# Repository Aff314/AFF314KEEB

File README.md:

# AFF314KEEB
A wireless 36-key low profile non split ergo keyboard.

I started to make this project because I really like using 36-key boards and I've even built two and a handwired board which I designed myself, but never somthing with a PCB. I'm really intersted in those kinds of projects and really like the ones others made but I've never really did one of my own. In the process of designing the board I've learned a lot on how to use KiCad and for the first time I actually documented what I was doing.

I want to thank [Joe Scotto](https://github.com/joe-scotto) for the KiCad footprints and symbols and for the great tutorials on designing a keyboard case and on ZMK.

Additionally I want to thank [GEIST](https://github.com/GEIGEIGEIST) for the Kicad footprints.

And lastly I want to thank [Kumamuk](https://github.com/kumamuk-git) for the CKW12 which made having a roller encoder possible since the EVQWGD001 is way too expensive.

## Instructions on buildung your own
If you want to build your own AFF314KEEB you should start to download the [Gerber file](PCB/Gerber.zip) and upload it to your prefered PCB manufacturing service and order it from there with the PCB from the CKW12 which you can find [here](https://github.com/kumamuk-git/CKW12).

You can find the rest of the parts in the [BOM](BOM.csv).

Once you have sourced all the parts you have to follow the [build guide](BUILDGUIDE.md).

## Partlist

Since I'm from Germany the prices were in EUR and I converted them to USD. Therefore they might not be one hundred percent accurate.

### Parts for the AFF314KEEB

| Item | Qty. | Total Price in USD | Link |
|------|------|--------------------|------|
| NRF52840 NineNano v2 Clone | 1 | 3.77 | https://de.aliexpress.com/item/1005006271779544.html |
| Kailh Choc Hot-Swap Socket | 36 | 6.25 | https://de.aliexpress.com/item/1005008928238101.html |
| Kailh Choc V1 Switch | 36 | 34.24 | https://de.aliexpress.com/item/1005008701630340.html |
| 1N4148W SOD123 | 37 | 1.64 | https://de.aliexpress.com/item/1005006123061230.html |
| IC-Sockets 12pin | 2 | 1.76 | https://de.aliexpress.com/item/1005007476809536.html |
| 3.7 V 301230 | 1 | 4.10 | https://42keebs.eu/shop/parts/lithium-polymer-battery/?attribute_size=301230%20(110%20mAh) |
| SKHLLCA010 | 1 | 0.71 | https://keeb.supply/products/alps-reset-button?variant=e834d428-bed6-4fb3-b94a-90e8f8b87d9b |
| MillMax Pins 3320-0-00-15-00-00-03-0 (optional) | 24 | 3.78 | https://keeb.supply/products/millmax-pins?variant=29bd2804-2a61-4fea-bfe3-f96557a35bd5 |
| PCB | 1 | 14.31 | https://github.com/Aff314/AFF314KEEB/blob/main/PCB/Gerber.zip |
| Any Keycaps for Choc V1 | 36 |  | https://github.com/braindefender/KLP-Lame-Keycaps/tree/master/STEP/Choc%20Stem%20%2B%20Choc%20Size |
| 3D Printed Case | 1 |  | https://github.com/Aff314/AFF314KEEB/tree/main/Case |
| Heatseat insert M2x3x3.5 | 8 | 2.54 | https://de.aliexpress.com/item/1005010362011631.html |
| M2 screws 5mm | 8 | 1.70 | https://de.aliexpress.com/item/1005005070119421.html |

### Parts for the CKW12

| Item | Qty. | Total Price in USD | Link |
|------|------|--------------------|------|
| SMD 3x6x2.5MM Tactile Button | 1 | 1.10 | https://de.aliexpress.com/item/1005008818216326.html |
| EC05E1220202 | 1 | 1.8 | https://de.aliexpress.com/item/1005007146553579.html |
| PCB | 1 | 2.40 | https://github.com/kumamuk-git/CKW12/tree/main/pcb/top |
| 3D Printed Housing | 1 |  | https://github.com/kumamuk-git/CKW12/blob/main/3dmodel/ckw12_housing.stp |
| 3D Printed Stem | 1 |  | https://github.com/kumamuk-git/CKW12/blob/main/3dmodel/ckw12_stem.stl |
| 3D Printed Wheel | 1 |  | https://github.com/kumamuk-git/CKW12/blob/main/3dmodel/ckw12_wheel_fix.stp |

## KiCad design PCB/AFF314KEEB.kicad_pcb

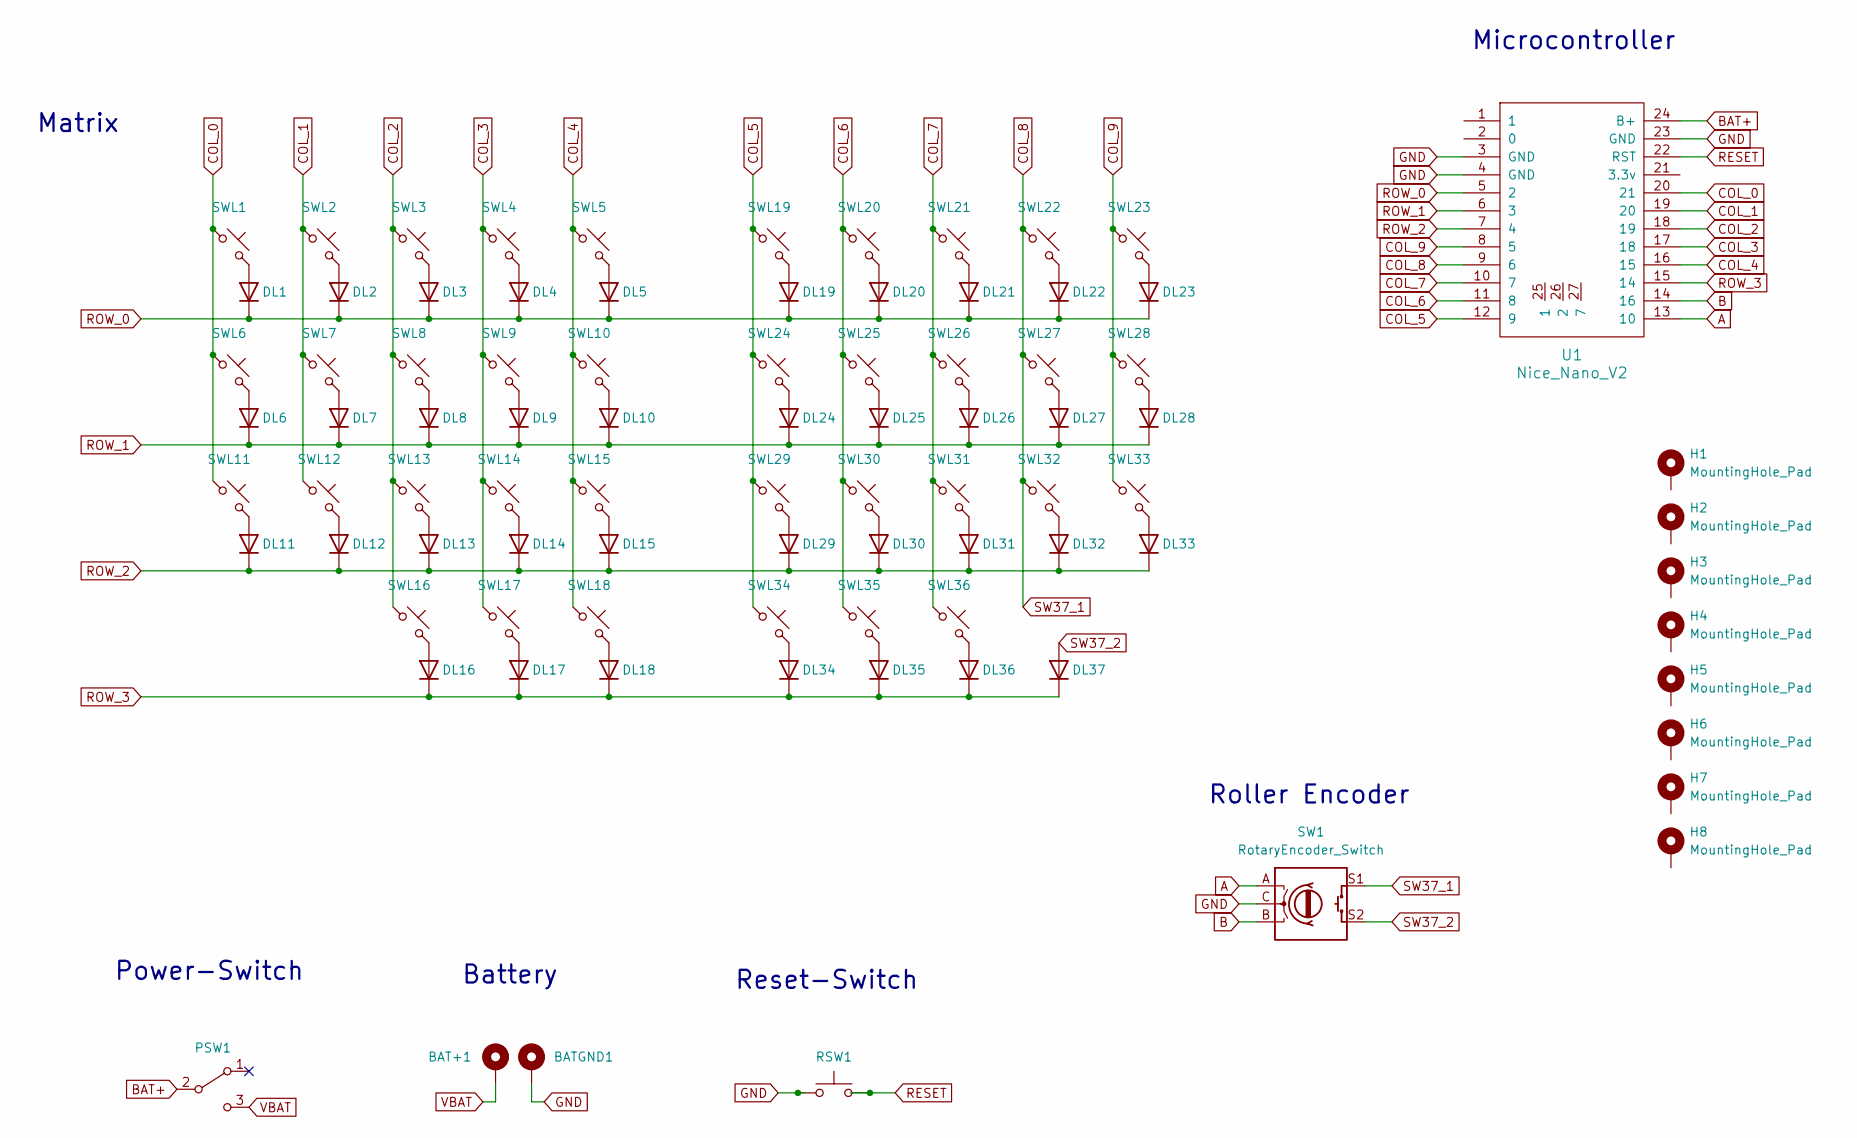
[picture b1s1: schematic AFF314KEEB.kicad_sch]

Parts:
BAT+1: +; BatteryPad
BATGND1: -; BatteryPad
DL1, DL2, DL3, DL4, DL5, DL6, DL7, DL8, DL9, DL10, DL11, DL12, DL13, DL14, DL15, DL16, DL17, DL18, DL19, DL20, DL21, DL22, DL23, DL24, DL25, DL26, DL27, DL28, DL29, DL30, DL31, DL32, DL33, DL34, DL35, DL36, DL37: D; Diode_SOD123
H1, H2, H3, H4, H5, H6, H7, H8: MountingHole_Pad; MountingHole_2.2mm_M2_DIN965_Pad_TopBottom
PSW1: SW_SPDT; MSK12C02
RSW1: SW_Push; SKHLLCA010
SW1: RotaryEncoder_Switch; CKW12
SWL1, SWL2, SWL3, SWL4, SWL5, SWL6, SWL7, SWL8, SWL9, SWL10, SWL11, SWL12, SWL13, SWL14, SWL15, SWL16, SWL17, SWL18, SWL19, SWL20, SWL21, SWL22, SWL23, SWL24, SWL25, SWL26, SWL27, SWL28, SWL29, SWL30, SWL31, SWL32, SWL33, SWL34, SWL35, SWL36: choc_v1_SW_solder; Kailh_socket_PG1350_optional
U1: Nice_Nano_V2; Nice_Nano_V2_Flipped

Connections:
A: SW1.A, U1.13 (10)
B: SW1.B, U1.14 (16)
BAT+: PSW1.2 (B), U1.24 (B+)
COL_0: SWL1.1, SWL6.1, SWL11.1, U1.20 (21)
COL_1: SWL2.1, SWL7.1, SWL12.1, U1.19 (20)
COL_2: SWL3.1, SWL8.1, SWL13.1, SWL16.1, U1.18 (19)
COL_3: SWL4.1, SWL9.1, SWL14.1, SWL17.1, U1.17 (18)
COL_4: SWL5.1, SWL10.1, SWL15.1, SWL18.1, U1.16 (15)
COL_5: SWL19.1, SWL24.1, SWL29.1, SWL34.1, U1.12 (9)
COL_6: SWL20.1, SWL25.1, SWL30.1, SWL35.1, U1.11 (8)
COL_7: SWL21.1, SWL26.1, SWL31.1, SWL36.1, U1.10 (7)
COL_8: SW1.S1, SWL22.1, SWL27.1, SWL32.1, U1.9 (6)
COL_9: SWL23.1, SWL28.1, SWL33.1, U1.8 (5)
GND: BATGND1.1, RSW1.1, SW1.C, U1.3 (GND), U1.4 (GND), U1.23 (GND)
unnamed: DL1.2 (A), SWL1.2
unnamed: DL2.2 (A), SWL2.2
unnamed: DL3.2 (A), SWL3.2
unnamed: DL4.2 (A), SWL4.2
unnamed: DL5.2 (A), SWL5.2
unnamed: DL6.2 (A), SWL6.2
unnamed: DL7.2 (A), SWL7.2
unnamed: DL8.2 (A), SWL8.2
unnamed: DL9.2 (A), SWL9.2
unnamed: DL10.2 (A), SWL10.2
unnamed: DL11.2 (A), SWL11.2
unnamed: DL12.2 (A), SWL12.2
unnamed: DL13.2 (A), SWL13.2
unnamed: DL14.2 (A), SWL14.2
unnamed: DL15.2 (A), SWL15.2
unnamed: DL16.2 (A), SWL16.2
unnamed: DL17.2 (A), SWL17.2
unnamed: DL18.2 (A), SWL18.2
unnamed: DL19.2 (A), SWL19.2
unnamed: DL20.2 (A), SWL20.2
unnamed: DL21.2 (A), SWL21.2
unnamed: DL22.2 (A), SWL22.2
unnamed: DL23.2 (A), SWL23.2
unnamed: DL24.2 (A), SWL24.2
unnamed: DL25.2 (A), SWL25.2
unnamed: DL26.2 (A), SWL26.2
unnamed: DL27.2 (A), SWL27.2
unnamed: DL28.2 (A), SWL28.2
unnamed: DL29.2 (A), SWL29.2
unnamed: DL30.2 (A), SWL30.2
unnamed: DL31.2 (A), SWL31.2
unnamed: DL32.2 (A), SWL32.2
unnamed: DL33.2 (A), SWL33.2
unnamed: DL34.2 (A), SWL34.2
unnamed: DL35.2 (A), SWL35.2
unnamed: DL36.2 (A), SWL36.2
RESET: RSW1.2, U1.22 (RST)
ROW_0: DL1.1 (K), DL2.1 (K), DL3.1 (K), DL4.1 (K), DL5.1 (K), DL19.1 (K), DL20.1 (K), DL21.1 (K), DL22.1 (K), DL23.1 (K), U1.5 (2)
ROW_1: DL6.1 (K), DL7.1 (K), DL8.1 (K), DL9.1 (K), DL10.1 (K), DL24.1 (K), DL25.1 (K), DL26.1 (K), DL27.1 (K), DL28.1 (K), U1.6 (3)
ROW_2: DL11.1 (K), DL12.1 (K), DL13.1 (K), DL14.1 (K), DL15.1 (K), DL29.1 (K), DL30.1 (K), DL31.1 (K), DL32.1 (K), DL33.1 (K), U1.7 (4)
ROW_3: DL16.1 (K), DL17.1 (K), DL18.1 (K), DL34.1 (K), DL35.1 (K), DL36.1 (K), DL37.1 (K), U1.15 (14)
SW37_2: DL37.2 (A), SW1.S2
VBAT: BAT+1.1, PSW1.3 (C)

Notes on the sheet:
Battery
Matrix
Reset-Switch
Microcontroller
Roller Encoder
Power-Switch

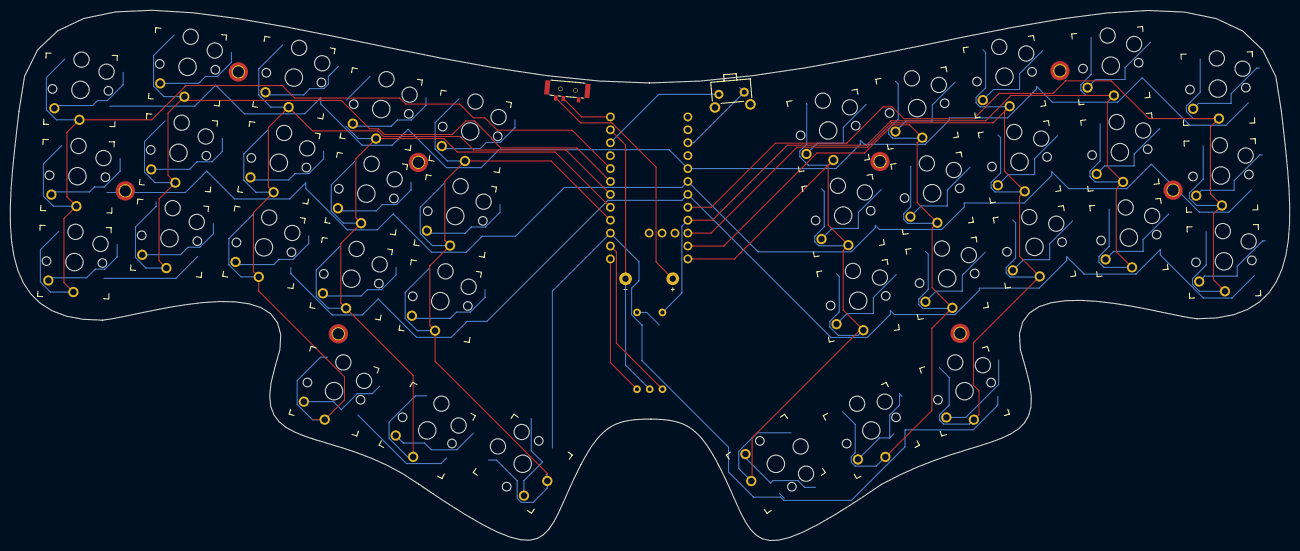
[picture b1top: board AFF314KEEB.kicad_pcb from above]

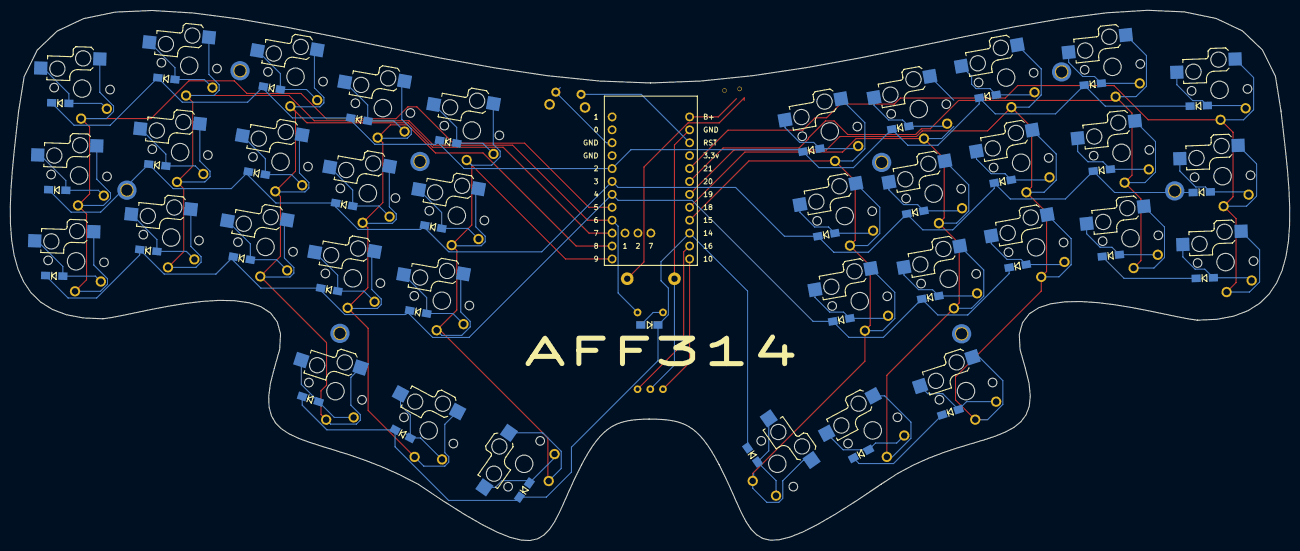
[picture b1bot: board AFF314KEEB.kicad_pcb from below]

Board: 2 copper layers, 251.7 x 104.3 mm, 87 parts (37 on the bottom side), 57 nets.

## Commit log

2026-02-26 Adding files
2026-02-27 Update keyboard description in README
2026-02-27 Add BOM and update case
2026-02-27 Update README with project details and instructions
    Expanded project description and added build instructions.
2026-02-27 Correct link to build guide in README.md
2026-02-27 Add PCB image to README
2026-02-27 Changed the front and back pics
2026-02-27 Add encoder to firmware and update step file
2026-02-27 Add part list for AFF314KEEB and CKW12
2026-02-27 Revise BUILDGUIDE.md with initial instructions
    Updated the build guide with sections on building the board and flashing firmware.
2026-02-27 Revise BUILDGUIDE.md for better readability
    Updated the build guide to improve formatting and clarity.
2026-02-27 Update README
    Added acknowledgments for contributors and resources.
2026-02-27 Add image of AFF314KEEB with case
    Added an image of the keyboard to the README.
2026-02-28 update
    Updated BOM.csv to include header row.
2026-02-28 Add Heatseat insert M2x3x3.5 to parts list
2026-02-28 Update BOM.csv with new items and adjustments
    Added a new item and updated quantities and prices in the BOM.
2026-02-28 small update
    Added missing header and rearranged item entries.
2026-02-28 Add 3.7 V 301230 battery to components list
2026-03-01 rename ZMK config folder
2026-03-01 remove unnecessary files and update step
2026-03-04 Small PCB tweak
2026-03-07 Replace case files
2026-03-07 Update case files
2026-04-09 case and firmware changed
2026-04-29 add picture
2026-04-29 Update image and improve README content
    Updated the image in the README and made minor text adjustments.
